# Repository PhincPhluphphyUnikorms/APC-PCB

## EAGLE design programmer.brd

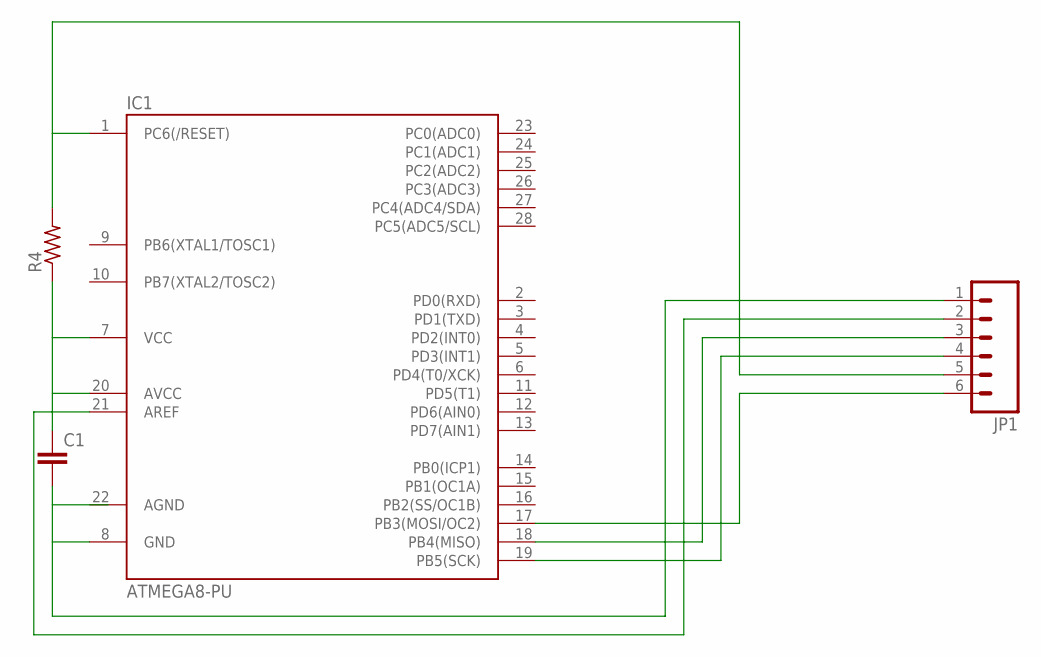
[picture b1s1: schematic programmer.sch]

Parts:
C1: C2.5/4; C2.5-4
IC1: ATMEGA8-PU; DIL28-3
JP1: M06LONGPADS; 1X06_LONGPADS
R4: R-US_0207/12; 0207/12

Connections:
AGND: IC1.22 (AGND)
unnamed: C1.2, IC1.8 (GND), JP1.1
unnamed: C1.1, IC1.7 (VCC), IC1.21 (AREF), JP1.2, R4.1
unnamed: IC1.18 (PB4(MISO)), JP1.3
unnamed: IC1.19 (PB5(SCK)), JP1.4
unnamed: IC1.1 (PC6(/RESET)), JP1.5, R4.2
unnamed: IC1.17 (PB3(MOSI/OC2)), JP1.6

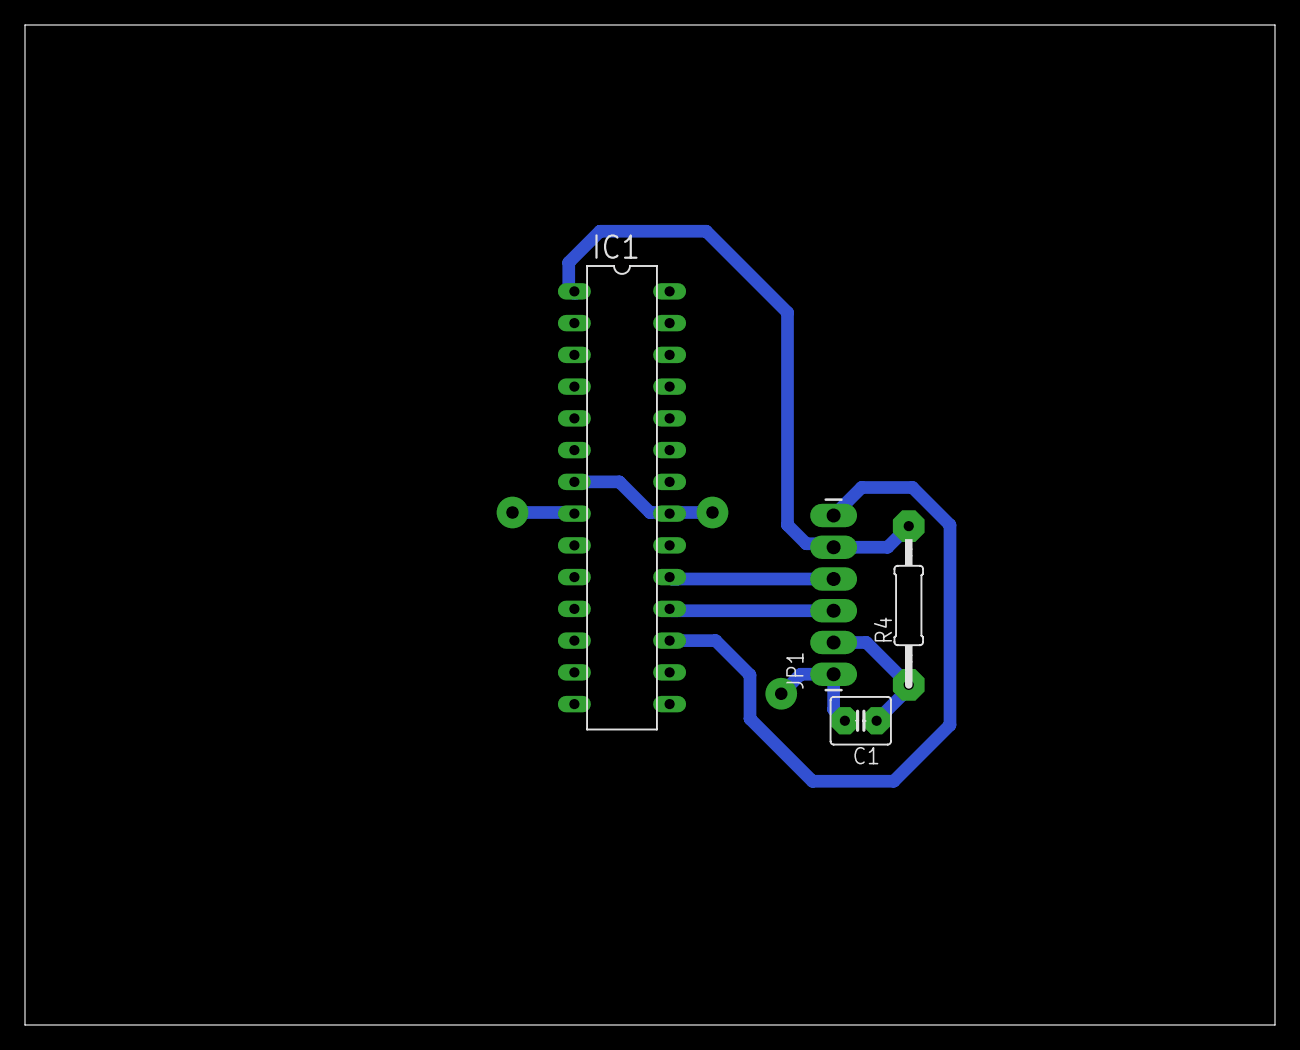
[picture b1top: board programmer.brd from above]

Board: 2 copper layers, 100.0 x 80.0 mm, 4 parts (0 on the bottom side), 6 nets.

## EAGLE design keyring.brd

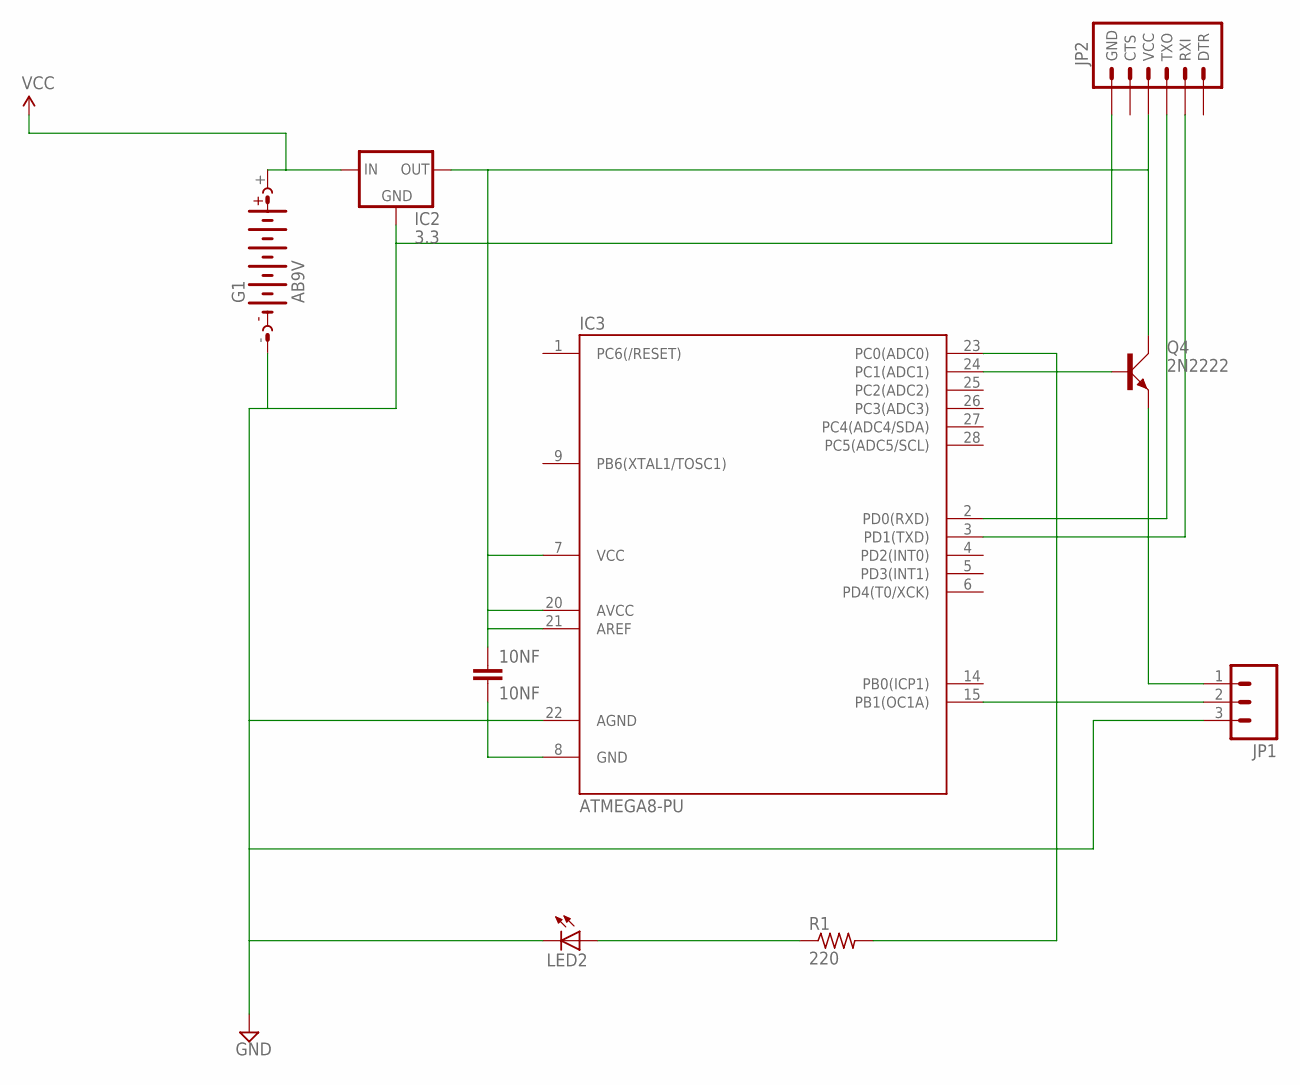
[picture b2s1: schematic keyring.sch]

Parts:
10NF: 10NF; C2.5-4
G1: AB9V
IC2: 3.3; TO220-IGO
IC3: ATMEGA8-PU; DIL28-3
JP1: M03LONGPADS; 1X03_LONGPADS
JP2: ARDUINO_SERIAL_PROGRAMLONGPADS; 1X06_LONGPADS
LED2: LED3MM
Q4: 2N2222; TO18A
R1: 220; 0207/12

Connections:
unnamed: IC3.24 (PC1(ADC1)), Q4.B
unnamed: IC3.3 (PD1(TXD)), JP2.2 (RXI)
unnamed: IC3.2 (PD0(RXD)), JP2.3 (TXO)
unnamed: JP1.1 (OUT), Q4.E
unnamed: IC3.23 (PC0(ADC0)), R1.2
unnamed: IC3.15 (PB1(OC1A)), JP1.2 (GND)
unnamed: LED2.A, R1.1
unnamed: 10NF.1, IC2.OUT, IC3.7 (VCC), IC3.20 (AVCC), IC3.21 (AREF), JP2.4 (VCC), Q4.C
unnamed: 10NF.2, G1.-, IC2.GND, IC3.8 (GND), IC3.22 (AGND), JP1.3 (VCC), JP2.6 (GND), LED2.K (C)
VCC: G1.+, IC2.IN

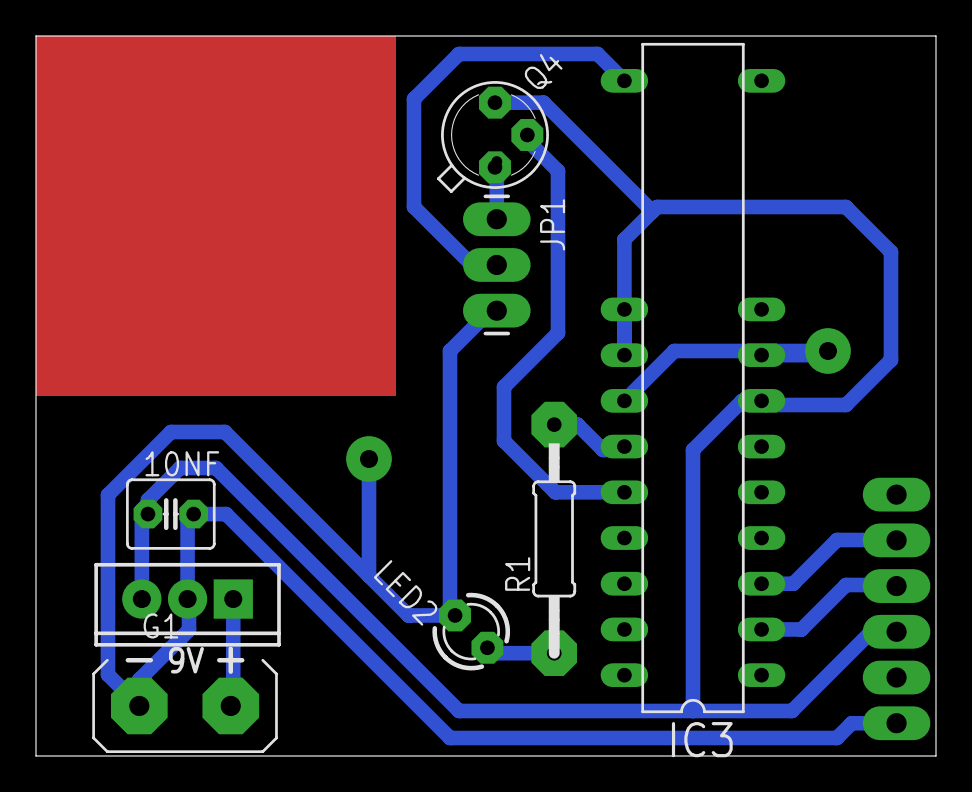
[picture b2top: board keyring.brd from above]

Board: 2 copper layers, 50.0 x 40.0 mm, 9 parts (1 on the bottom side), 10 nets.

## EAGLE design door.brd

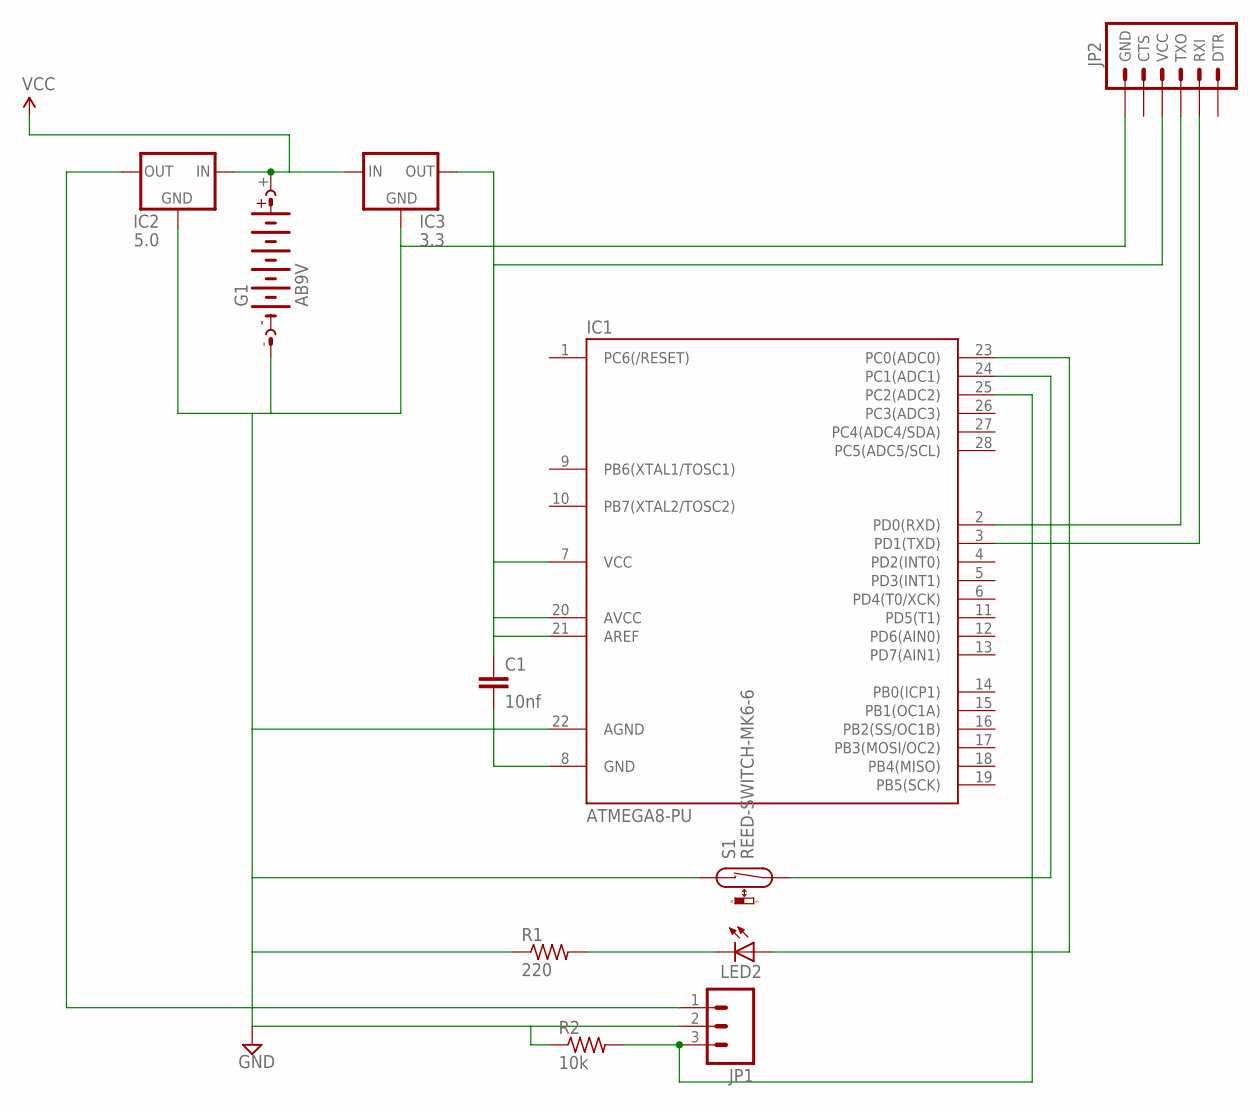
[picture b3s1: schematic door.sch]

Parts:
C1: 10nf; C2.5-4
G1: AB9V
IC1: ATMEGA8-PU; DIL28-3
IC2: 5.0; TO220-IGO
IC3: 3.3; TO220-IGO
JP1: M03PTH; 1X03
JP2: ARDUINO_SERIAL_PROGRAMLONGPADS; 1X06_LONGPADS
LED2: LED3MM
R1: 220; 0207/12
R2: 10k; 0207/12
S1: REED-SWITCH-MK6-6; MK6-6

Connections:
GND: C1.2, G1.-, IC1.8 (GND), IC1.22 (AGND), IC2.GND, IC3.GND, JP1.2 (GND), JP2.6 (GND), R1.1, R2.1, S1.1
unnamed: IC2.OUT, JP1.1 (OUT)
unnamed: IC1.3 (PD1(TXD)), JP2.2 (RXI)
unnamed: IC1.2 (PD0(RXD)), JP2.3 (TXO)
unnamed: IC1.24 (PC1(ADC1)), S1.2
unnamed: IC1.23 (PC0(ADC0)), LED2.A
unnamed: IC1.25 (PC2(ADC2)), JP1.3 (VCC), R2.2
unnamed: LED2.K (C), R1.2
unnamed: C1.1, IC1.7 (VCC), IC1.20 (AVCC), IC1.21 (AREF), IC3.OUT, JP2.4 (VCC)
VCC: G1.+, IC2.IN, IC3.IN

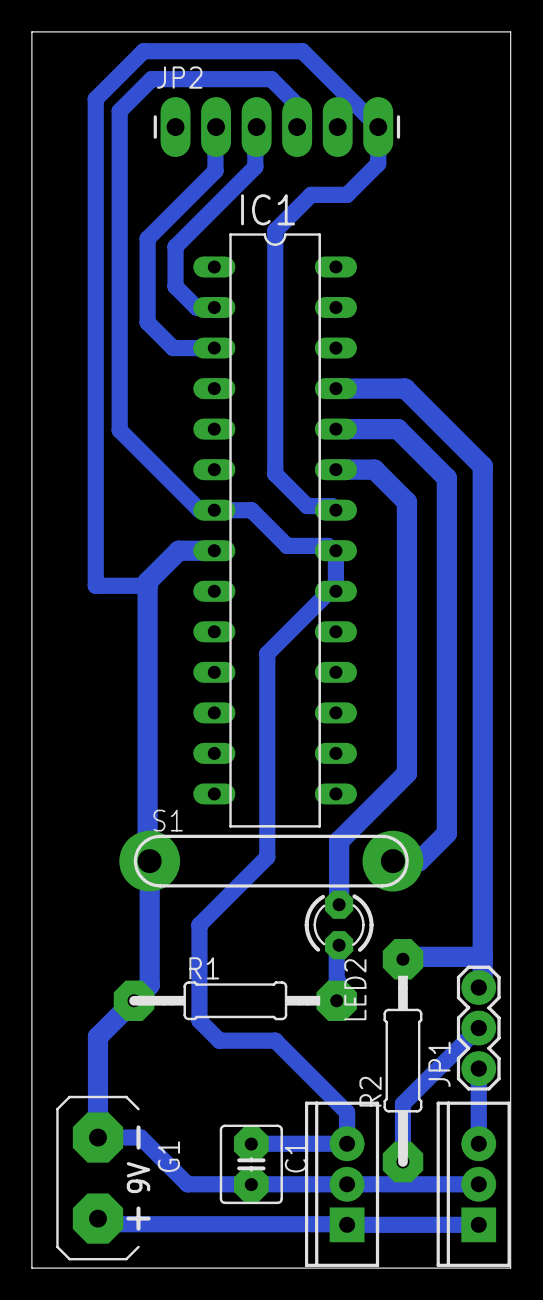
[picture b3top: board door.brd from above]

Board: 2 copper layers, 30.0 x 77.5 mm, 11 parts (0 on the bottom side), 10 nets.

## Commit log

2015-10-19 UUUHHHH FIRST COMMIT WUUUUHUUUU
2015-10-19 bigger pads
2015-10-19 bigger pads nbow with export
2015-10-19 added keyboard
2015-10-19 added programmer

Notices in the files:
parts and their libraries:
SparkFun: Licensing: CC v3.0 Share-Alike You are welcome to use this library for commercial purposes.
